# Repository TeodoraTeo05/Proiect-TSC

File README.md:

# Proiect TSC 2025 – OpenBook

## Descriere generală

OpenBook este un dispozitiv portabil de tip e-book reader bazat pe ESP32-C6. Dispozitivul conține un ecran e-paper, butoane de control, senzor de mediu, ceas de timp real și posibilitate de alimentare de la baterie Li-Po, fiind gândit ca un sistem eficient energetic și scalabil.
---

#### 1 Diagramă bloc

---
## 2 BOM (Bill of Materials)

| Part | Device | Datasheet |
|------|--------|-----------|
| CHG_LED | ADAFRUIT_LEDCHIP-LED0603 | [ADAFRUIT_LEDCHIP-LED0603](N/A) |
| SJ1 | SJ | [SJ](N/A) |
| EPD_C5 | EAGLE-LTSPICE_CC0402 | [EAGLE-LTSPICE_CC0402](N/A) |
| R3 | ESP32_WROVER_EAGLE-LTSPICE_RR0402 | [ESP32_WROVER_EAGLE-LTSPICE_RR0402](N/A) |
| R1_PWRUSB | ESP32_WROVER_EAGLE-LTSPICE_RR0402 | [ESP32_WROVER_EAGLE-LTSPICE_RR0402](N/A) |
| C4_USB | EAGLE-LTSPICE_CC0402 | [EAGLE-LTSPICE_CC0402](N/A) |
| C1, C2, C6, C8, C9, C10, C_DELAY | ESP32_WROVER_EAGLE-LTSPICE_CC0402 | [ESP32_WROVER_EAGLE-LTSPICE_CC0402](N/A) |
| C3 | RCL_CPOL-EUCT3528 | [RCL_CPOL-EUCT3528](N/A) |
| R1, R1_PINH, R1_PINH1, R2_PINH, R2_PINH1, R4, R5, R6, R7, R8, R9, R10, R_BOOT, R_CHANGE, R_CL1, R_RESET | ESP32_WROVER_EAGLE-LTSPICE_RR0402 | [ESP32_WROVER_EAGLE-LTSPICE_RR0402](N/A) |
| C7 | ESP32_WROVER_EAGLE-LTSPICE_CC0402 | [ESP32_WROVER_EAGLE-LTSPICE_CC0402](N/A) |
| J4 | 112A-TAAR-R03_ATTEND | [112A-TAAR-R03_ATTEND](N/A) |
| R_CAPACITOR | ESP32_WROVER_EAGLE-LTSPICE_RR0402 | [ESP32_WROVER_EAGLE-LTSPICE_RR0402](N/A) |
| C5 | ESP32_WROVER_EAGLE-LTSPICE_CC0402 | [ESP32_WROVER_EAGLE-LTSPICE_CC0402](N/A) |
| EPD_C6, EPD_C7, EPD_C8, EPD_C9, EPD_C10, EPD_C11, EPD_C12 | EAGLE-LTSPICE_CC0402 | [EAGLE-LTSPICE_CC0402](N/A) |
| EPD_C1, EPD_C2 | ESP32_WROVER_EAGLE-LTSPICE_CC0402 | [ESP32_WROVER_EAGLE-LTSPICE_CC0402](N/A) |
| R2 | ESP32_WROVER_EAGLE-LTSPICE_RR0402 | [ESP32_WROVER_EAGLE-LTSPICE_RR0402](N/A) |
| R1_BAT | ESP32_WROVER_EAGLE-LTSPICE_RR0402 | [ESP32_WROVER_EAGLE-LTSPICE_RR0402](N/A) |
| Q1, Q2 | ESP32_WROVER_SPARKFUN-DISCRETESEMI_MOSFET_PCH-DMG2305UX-7 | [ESP32_WROVER_SPARKFUN-DISCRETESEMI_MOSFET_PCH-DMG2305UX-7](N/A) |
| R2_BAT | ESP32_WROVER_EAGLE-LTSPICE_RR0402 | [ESP32_WROVER_EAGLE-LTSPICE_RR0402](N/A) |
| C5_USB | EAGLE-LTSPICE_CC0402 | [EAGLE-LTSPICE_CC0402](N/A) |
| C1_BAT, C1_BAT1, C1_BAT2, C2_BAT | ESP32_WROVER_EAGLE-LTSPICE_CC0402 | [ESP32_WROVER_EAGLE-LTSPICE_CC0402](N/A) |
| C4 | ESP32_WROVER_EAGLE-LTSPICE_CC0402 | [ESP32_WROVER_EAGLE-LTSPICE_CC0402](N/A) |
| R2-USB, R2-USB1 | ESP32_WROVER_EAGLE-LTSPICE_RR0402 | [ESP32_WROVER_EAGLE-LTSPICE_RR0402](N/A) |
| L1 | 744043680IND_4828-WE-TPC_WRE | [744043680IND_4828-WE-TPC_WRE](N/A) |
| IC1 | BD5229G-TR | [BD5229G-TR](N/A) |
| SENSOR2 | ESP32_WROVER_BME680_BME680 | [ESP32_WROVER_BME680_BME680](N/A) |
| U$2 | BUTTON_CUSYOMV1 | [BUTTON_CUSYOMV1](N/A) |
| U$3 | BUTTON_CUSYOMV1 | [BUTTON_CUSYOMV1](N/A) |
| C10_SUPERCAP | CPH3225A | [CPH3225A](https://www.snapeda.com/parts/CPH3225A/Seiko+Instruments/view-part/?ref=snap) |
| U3 | DS3231SN# | [DS3231SN#](https://www.snapeda.com/parts/DS3231SN%23/Analog+Devices/view-part/?ref=snap) |
| U2 | ESP32-C6-WROOM-1-N8 | [ESP32-C6-WROOM-1-N8](N/A) |
| PFMF.050.1 | ESP32C6_VARISTORCN1812 | [ESP32C6_VARISTORCN1812](N/A) |
| D2, D7 | ESP32_WROVER_AVX---SD0805S020S1R0_AVX_SD0805S020S1R0_0_0AVX_SD0805S020S1R0_0_0 | [ESP32_WROVER_AVX---SD0805S020S1R0_AVX_SD0805S020S1R0_0_0AVX_SD0805S020S1R0_0_0](N/A) |
| MCP73831 | ESP32_WROVER_SPARKFUN-IC-POWER_MCP73831 | [ESP32_WROVER_SPARKFUN-IC-POWER_MCP73831](N/A) |
| J1 | FH34SRJ-24S-0.5SH_99_ | [FH34SRJ-24S-0.5SH_99_](N/A) |
| U4 | MAX17048G+T10 | [MAX17048G+T10](https://www.snapeda.com/parts/MAX17048G+T10/Analog+Devices/view-part/?ref=snap) |
| D3, D4, D5 | MBR0530 | [MBR0530](https://www.snapeda.com/parts/MBR0530/Onsemi/view-part/?ref=snap) |
| D6, D8, D9, D10, D11, D12 | PGB1010603MR | [PGB1010603MR](https://www.snapeda.com/parts/PGB1010603MR/Littelfuse/view-part/?ref=snap) |
| J3 | QWIIC_CONNECTORJS-1MM | [QWIIC_CONNECTORJS-1MM](N/A) |
| U$1 | BUTTON_CUSYOMV1 | [BUTTON_CUSYOMV1](N/A) |
| J2 | SAMACSYS_PARTS_USB4110-GF-A | [SAMACSYS_PARTS_USB4110-GF-A](N/A) |
| Q3 | SI1308EDL-T1-GE3 | [SI1308EDL-T1-GE3](N/A) |
| TP1, TP2, TP3, TP4, TP5, TP6, TP7, TP8, TP9, TP10, TP11, TP12, TP13, TP14, TP15, TP16, TP17 | TPTP20R | [facut de mine] |
| D1 | USBLC6-2SC6Y | [USBLC6-2SC6Y](https://www.snapeda.com/parts/USBLC6-2SC6Y/STMicroelectronics/view-part/?ref=snap) |
| U1 | W25Q512JVEIQ | [W25Q512JVEIQ](https://www.snapeda.com/parts/W25Q512JVEIQ/Winbond+Electronics/view-part/?ref=snap) |
| IC4 | XC6220A331MR-G | [XC6220A331MR-G](N/A) |

## 3. Funcționalitate hardware

Proiectul OpenBook este un cititor de tip e-paper, alimentat din baterie LiPo și construit în jurul microcontrollerului ESP32-C3-WROOM. 
Dispozitivul colectează date de mediu (temperatură, umiditate, CO2, particule), le salvează pe card microSD și le poate afișa pe ecranul e-paper.

### ESP32-C3-WROOM
- Modulul principal cu conectivitate Wi-Fi/BLE, capabil să comunice prin SPI, I2C și UART.
- Tensiune de alimentare: 3.3V, furnizată de LDO.

### Sistem de alimentare
- **USB-C** este utilizat pentru încărcare și comunicare USB.
- **MCP73832** gestionează încărcarea bateriei LiPo.
- **LDO 3.3V** alimentează ESP32 și restul componentelor la 3.3V.
- **DC/DC 5V** generează 5V pentru senzorii care necesită tensiune mai mare (PM și CO2).

### Senzori
- **BME680** - senzor de temperatură, umiditate și gaze, comunică prin I2C.
- **MH-Z19B** - senzor de CO2 alimentat la 5V, comunică prin UART.
- **PMSA003** - senzor pentru particule fine (PM2.5), comunică prin UART, 5V.

### Afișaj
- Display e-paper monocrom de 1.5" cu rezoluție 200x200 px.
- Interfață SPI comună cu SD Card-ul.

### SD Card
- Modul pentru stocarea datelor colectate sau a fișierelor text.
- Interfață SPI.

### Butoane
- 3 butoane tactile conectate la GPIO pentru control interfață (ex. navigare meniu, refresh ecran).

### Calcule de consum estimativ (valori medii)

| Modul                | Tensiune | Curent (mA) | Consum estimativ |
|----------------------|----------|-------------|------------------|
| ESP32-C3             | 3.3V     | 80-150       | 0.3-0.5W         |
| E-Ink Display        | 3.3V     | 10 (refresh) | 0.03W            |
| BME680               | 3.3V     | 2-3          | 0.01W            |
| MH-Z19B              | 5V       | 40-50        | 0.25W            |
| PMSA003              | 5V       | 60-100       | 0.5W             |
| SD Card              | 3.3V     | 10           | 0.03W            |
| MCP73832 (charger)   | 5V       | 1000 (max)   | doar când încarcă |

**Modul deep sleep:** Consum sub 1 mA total. Ideal pentru dispozitiv portabil.

## 4. Pinout ESP32-C3

| Pin ESP32-C3     | Componentă                 | Motiv / Semnal                          |
|------------------|------------------------------|-----------------------------------------|
| GPIO1 (I2C SDA)  | BME680                       | Comunicație I2C                       |
| GPIO2 (I2C SCL)  | BME680                       | Comunicație I2C                       |
| GPIO3 (UART RX)  | PMSA003                      | UART RX senzor PM                       |
| GPIO4 (SPI CS SD)| SD Card                      | Chip Select SD Card                     |
| GPIO5            | E-Ink DC                     | Date/Command E-Ink                      |
| GPIO6 (SPI CLK)  | E-Ink & SD                   | Clock SPI                              |
| GPIO7 (SPI MOSI) | E-Ink & SD                   | Date SPI                               |
| GPIO8 (GPIO)     | Buton 1                      | Control meniu / page flip              |
| GPIO9 (GPIO)     | Buton 2                      | Control meniu / page flip              |
| GPIO10 (SPI CS)  | E-Ink Display                | Chip Select e-paper                    |
| GPIO11 (SPI CS)  | Flash extern (opțional)     | N/A                                    |
| GPIO12 (USB D-)  | USB                          | Comunicație USB                       |
| GPIO13 (USB D+)  | USB                          | Comunicație USB                       |
| GPIO18           | MH-Z19B (UART TX)            | UART pentru senzor CO2                 |
| GPIO19           | Buton 3                      | Navigare / confirmare                  |

## 5. Alte aspecte relevante

- Designul PCB respectă recomandările de trasee de putere (min 0.3mm), semnale (min 0.15mm).
- Antena ESP32-C3 este amplasată spre exteriorul plăcii, iar zona de sub ea este decupată.
- Condensatoarele de decuplare sunt apropiate de VCC-ul componentelor.
- Plan de masă solid pe ambele layere și via stitching activ.
- Toate componentele pasive sunt SMD 0402.
- Layout-ul este proiectat în Fusion360, aliniat cu dimensiunile carcasei fizice.
- Imaginile randate ale dispozitivului și carcasei se găsesc în folderul `Images/` din acest repository.

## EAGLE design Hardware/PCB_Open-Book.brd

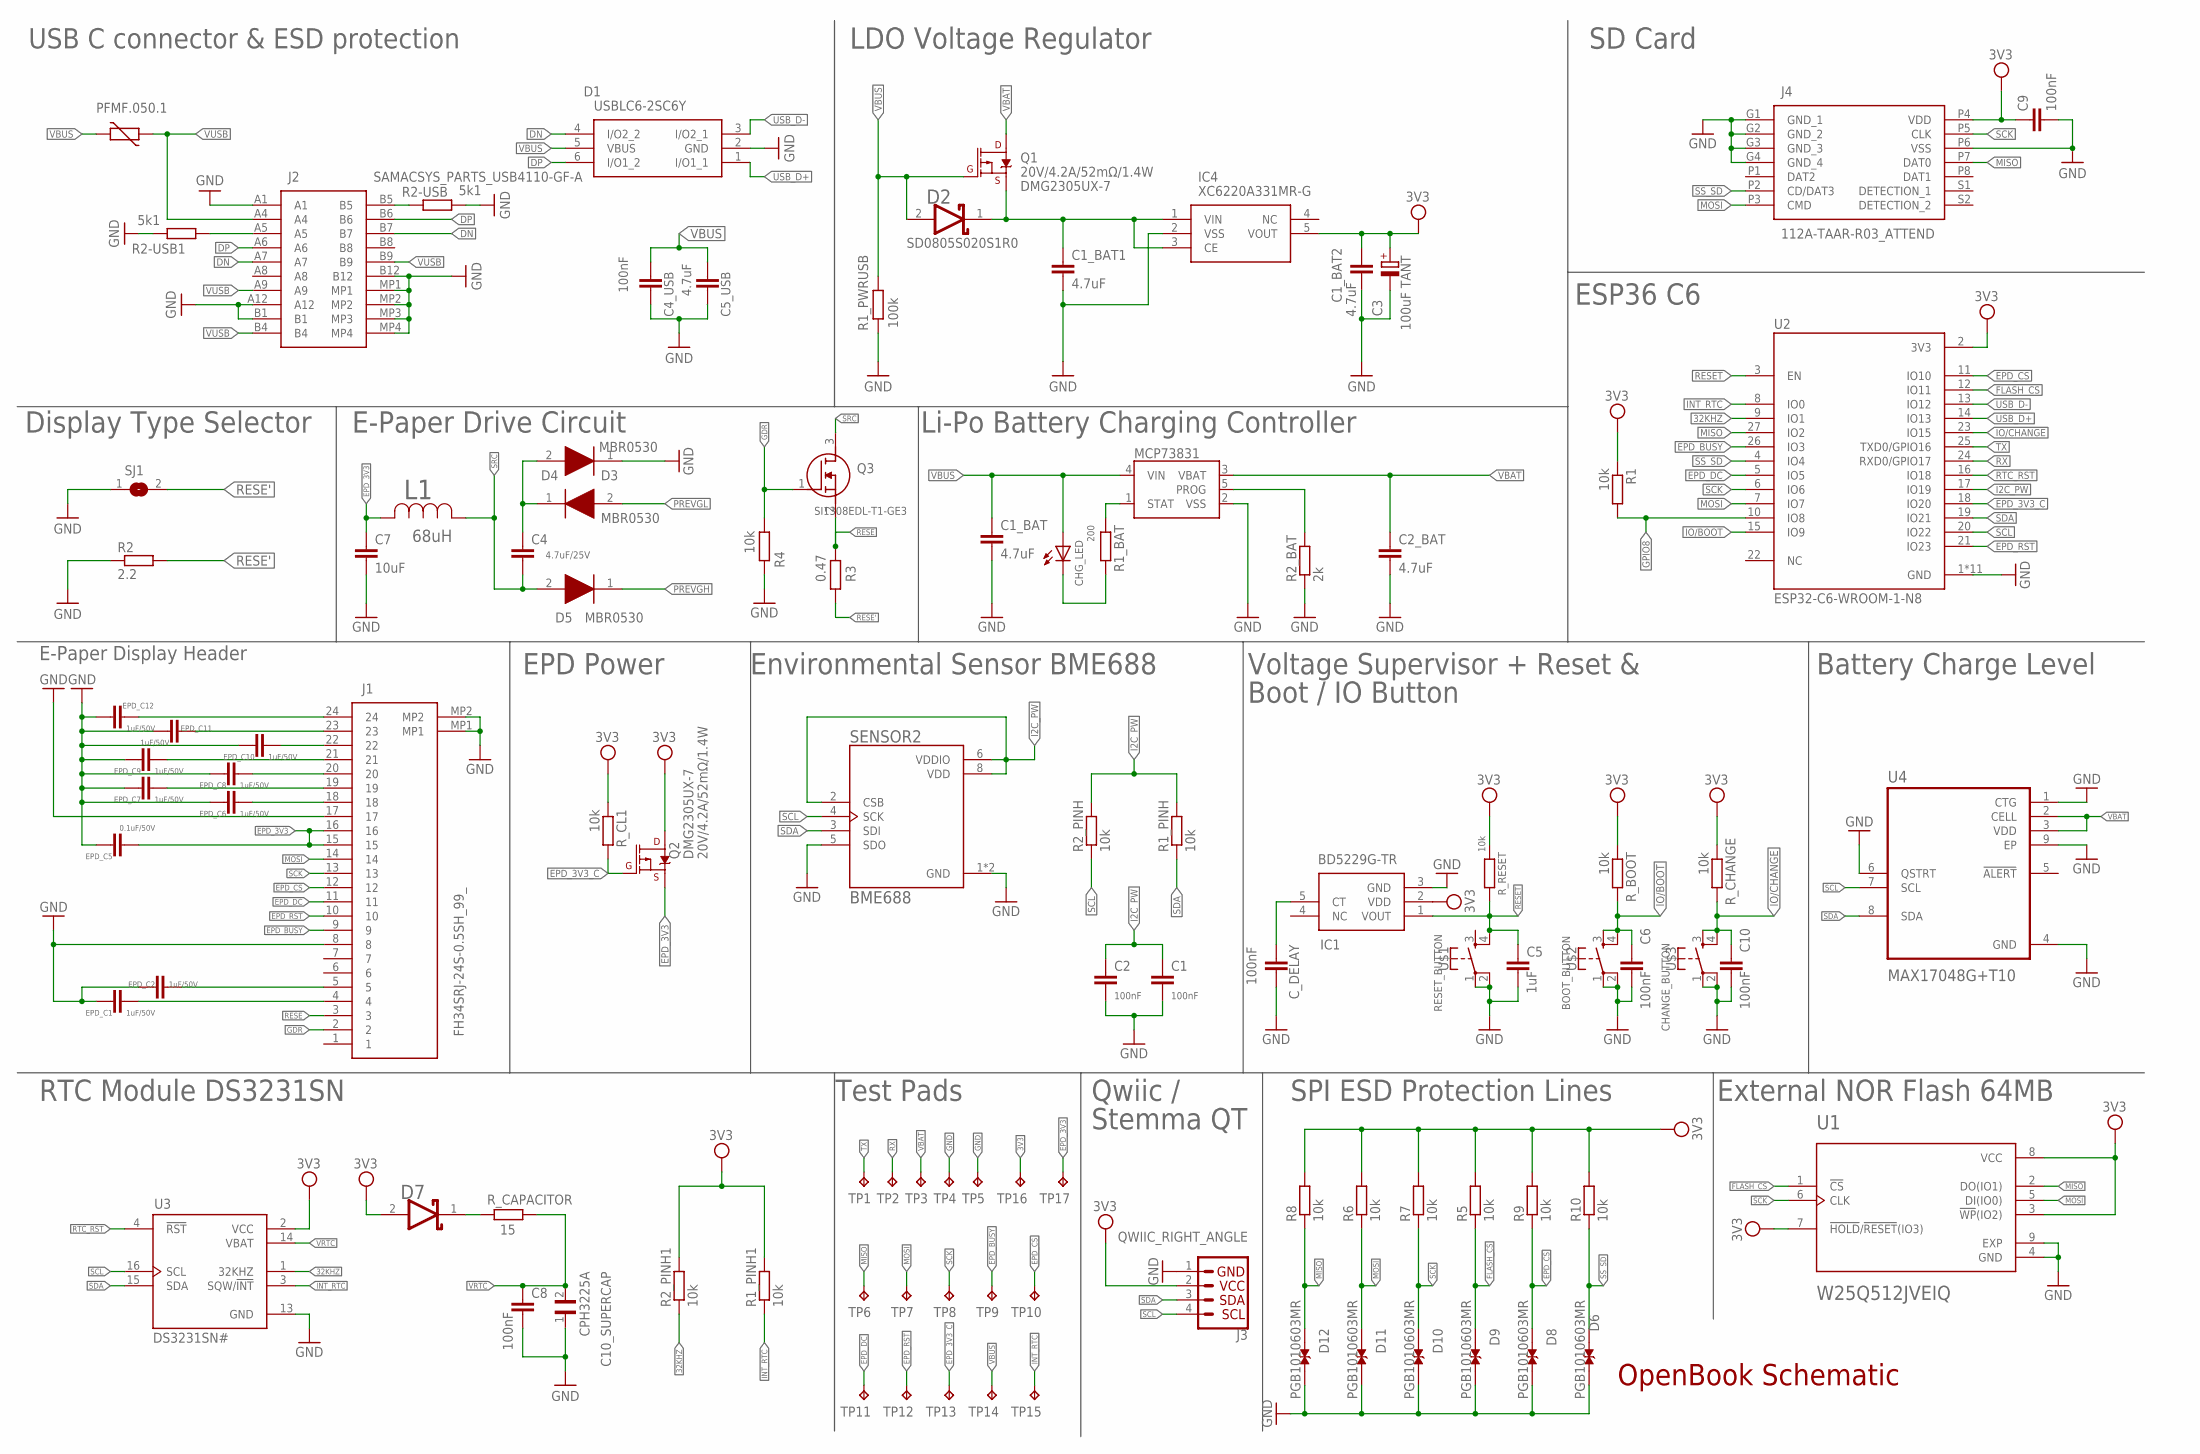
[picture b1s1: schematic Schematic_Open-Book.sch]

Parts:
C1, C2, C6, C8, C9, C10: 100nF; ESP32_WROVER_EAGLE-LTSPICE_C0402
C1_BAT, C1_BAT1, C1_BAT2, C2_BAT: 4.7uF; ESP32_WROVER_EAGLE-LTSPICE_C0402
C3: 100uF TANT; RCL_CT3528
C4: 4.7uF/25V; ESP32_WROVER_EAGLE-LTSPICE_C0402
C4_USB: 100nF; EAGLE-LTSPICE_C0402
C5: 1uF; ESP32_WROVER_EAGLE-LTSPICE_C0402
C5_USB: 4.7uF; EAGLE-LTSPICE_C0402
C7: 10uF; ESP32_WROVER_EAGLE-LTSPICE_C0402
C10_SUPERCAP: CPH3225A; CAPCP3225X100N
CHG_LED: ADAFRUIT_LEDCHIP-LED0603; ADAFRUIT_CHIP-LED0603
C_DELAY: 100nF; ESP32_WROVER_EAGLE-LTSPICE_C0402
D1: USBLC6-2SC6Y; SOT95P280X145-6N
D2, D7: ESP32_WROVER_AVX---SD0805S020S1R0_AVX_SD0805S020S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; ESP32_WROVER_AVX---SD0805S020S1R0_AVX_SD0805S020S1R0_0
D3, D4, D5: MBR0530; SOD3716X135N
D6, D8, D9, D10, D11, D12: PGB1010603MR; DIOC1608X36N
EPD_C1, EPD_C2: 1uF/50V; ESP32_WROVER_EAGLE-LTSPICE_C0402
EPD_C5: 0.1uF/50V; EAGLE-LTSPICE_C0402
EPD_C6, EPD_C7, EPD_C8, EPD_C9, EPD_C10, EPD_C11, EPD_C12: 1uF/50V; EAGLE-LTSPICE_C0402
IC1: BD5229G-TR; SOT95P280X125-5N
IC4: XC6220A331MR-G; SOT95P280X120-5N
J1: FH34SRJ-24S-0.5SH_99_; FH34SRJ24S05SH99
J2: SAMACSYS_PARTS_USB4110-GF-A; SAMACSYS_PARTS_USB4110GFA
J3: QWIIC_RIGHT_ANGLE; JST04_1MM_RA
J4: 112A-TAAR-R03_ATTEND; 112ATAARR03ATTEND
L1: 68uH; IND_4828-WE-TPC_WRE
MCP73831: ESP32_WROVER_SPARKFUN-IC-POWER_MCP73831; ESP32_WROVER_SPARKFUN-IC-POWER_SOT23-5
PFMF.050.1: ESP32C6_VARISTORCN1812; ESP32C6_VARISTOR_CT/CN1812
Q1, Q2: 20V/4.2A/52mΩ/1.4W; ESP32_WROVER_SPARKFUN-DISCRETESEMI_SOT23-3
Q3: SI1308EDL-T1-GE3; SOT65P210X110-3N
R1, R1_PINH, R1_PINH1, R2_PINH, R2_PINH1, R4, R5, R6, R7, R8, R9, R10: 10k; ESP32_WROVER_EAGLE-LTSPICE_R0402
R1_BAT: 200; ESP32_WROVER_EAGLE-LTSPICE_R0402
R1_PWRUSB: 100k; ESP32_WROVER_EAGLE-LTSPICE_R0402
R2: 2.2; ESP32_WROVER_EAGLE-LTSPICE_R0402
R2-USB, R2-USB1: 5k1; ESP32_WROVER_EAGLE-LTSPICE_R0402
R2_BAT: 2k; ESP32_WROVER_EAGLE-LTSPICE_R0402
R3: 0.47; ESP32_WROVER_EAGLE-LTSPICE_R0402
R_BOOT: 10k; ESP32_WROVER_EAGLE-LTSPICE_R0402
R_CAPACITOR: 15; ESP32_WROVER_EAGLE-LTSPICE_R0402
R_CHANGE: 10k; ESP32_WROVER_EAGLE-LTSPICE_R0402
R_CL1: 10k; ESP32_WROVER_EAGLE-LTSPICE_R0402
R_RESET: 10k; ESP32_WROVER_EAGLE-LTSPICE_R0402
SENSOR2: BME688; ESP32_WROVER_BME680_PSON80P300X300X100-8N
SJ1: SJ
TP1, TP2, TP3, TP4, TP5, TP6, TP7, TP8, TP9, TP10, TP11, TP12, TP13, TP14, TP15, TP16, TP17: TPTP20R; TP20R
U1: W25Q512JVEIQ; SON127P600X800X80-9N
U2: ESP32-C6-WROOM-1-N8; XCVR_ESP32-C6-WROOM-1-N8
U3: DS3231SN#; SOIC127P1032X265-16N
U4: MAX17048G+T10; SON50P200X200X80-9N
U$1: RESET_BUTTON; MYBUTTON
U$2: BOOT_BUTTON; MYBUTTON
U$3: CHANGE_BUTTON; MYBUTTON

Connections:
3V3: C1_BAT2.1, C3.+, C9.1, D7.2 (ANODE), IC1.2 (VDD), IC4.5 (VOUT), J3.2, J4.P4 (VDD), Q2.3 (D), R1.1, R1_PINH1.2, R2_PINH1.2, R5.2, R6.2, R7.2, R8.2, R9.2, R10.2, R_BOOT.1, R_CHANGE.1, R_CL1.1, R_RESET.1, TP16.TP, U1.3 (!WP!(IO2)), U1.7 (!HOLD!/!RESET!(IO3)), U1.8 (VCC), U2.2 (3V3), U3.2 (VCC)
32KHZ: R2_PINH1.1, U2.9 (IO1), U3.1 (32KHZ)
DN: D1.4 (I/O2_2), J2.A7, J2.B7
DP: D1.6 (I/O1_2), J2.A6, J2.B6
EPD_3V3: C7.1, EPD_C5.1, J1.15, J1.16, L1.2, Q2.2 (S), TP17.TP
EPD_3V3_C: Q2.1 (G), R_CL1.2, TP13.TP, U2.18 (IO20)
EPD_BUSY: J1.9, TP9.TP, U2.26 (IO3)
EPD_CS: D8.1, J1.12, R9.1, TP10.TP, U2.11 (IO10)
EPD_DC: J1.11, TP11.TP, U2.5 (IO5)
EPD_RST: J1.10, TP12.TP, U2.21 (IO23)
FLASH_CS: D9.1, R5.1, U1.1 (!CS), U2.12 (IO11)
GDR: J1.2, Q3.1 (G), R4.2
GND: C1.2, C1_BAT.2, C1_BAT1.2, C1_BAT2.2, C2.2, C2_BAT.2, C3.-, C4_USB.2, C5.2, C5_USB.2, C6.2, C7.2, C8.2, C9.2, C10.2, C10_SUPERCAP.1, C_DELAY.2, D1.2 (GND), D4.1 (K), D6.2, D8.2, D9.2, D10.2, D11.2, D12.2, EPD_C1.2, EPD_C2.2, EPD_C5.2, EPD_C6.2, EPD_C7.2, EPD_C8.2, EPD_C9.2, EPD_C10.2, EPD_C11.2, EPD_C12.2, IC1.3 (GND), IC4.2 (VSS), J1.8, J1.17, J1.MP1, J1.MP2, J2.A1, J2.A12, J2.B1, J2.B12, J2.MP1, J2.MP2, J2.MP3, J2.MP4, J3.1, J4.G1 (GND_1), J4.G2 (GND_2), J4.G3 (GND_3), J4.G4 (GND_4), J4.P6 (VSS), MCP73831.2 (VSS), R1_PWRUSB.2, R2.1, R2-USB.2, R2-USB1.1, R2_BAT.1, R4.1, SENSOR2.1 (GND), SENSOR2.5 (SDO), SENSOR2.7 (GND), SJ1.1, TP4.TP, TP5.TP, U1.4 (GND), U1.9 (EXP), U2.1 (GND), U2.28 (GND), U2.29_1 (GND), U2.29_2 (GND), U2.29_3 (GND), U2.29_4 (GND), U2.29_5 (GND), U2.29_6 (GND), U2.29_7 (GND), U2.29_8 (GND), U2.29_9 (GND), U3.13 (GND), U4.1 (CTG), U4.4 (GND), U4.6 (QSTRT), U4.9 (EP), U$1.1, U$1.2, U$2.1, U$2.2, U$3.1, U$3.2
GPIO8: R1.2, U2.10 (IO8)
I2C_PW: C1.1, C2.1, R1_PINH.2, R2_PINH.2, SENSOR2.2 (CSB), SENSOR2.6 (VDDIO), SENSOR2.8 (VDD), U2.17 (IO19)
INT_RTC: R1_PINH1.1, TP15.TP, U2.8 (IO0), U3.3 (SQW/!INT)
IO/BOOT: C6.1, R_BOOT.2, U2.15 (IO9), U$2.3, U$2.4
IO/CHANGE: C10.1, R_CHANGE.2, U2.23 (IO15), U$3.3, U$3.4
MISO: D12.1, J4.P7 (DAT0), R8.1, TP6.TP, U1.2 (DO(IO1)), U2.27 (IO2)
MOSI: D11.1, J1.14, J4.P3 (CMD), R6.1, TP7.TP, U1.5 (DI(IO0)), U2.7 (IO7)
unnamed: J2.B5, R2-USB.1
unnamed: J2.A5, R2-USB1.2
unnamed: C4.1, D3.1 (K), D4.2 (A)
unnamed: C1_BAT1.1, D2.1 (CATHODE), IC4.1 (VIN), IC4.3 (CE), Q1.2 (S)
unnamed: MCP73831.5 (PROG), R2_BAT.2
unnamed: CHG_LED.C, R1_BAT.2
unnamed: MCP73831.1 (STAT), R1_BAT.1
unnamed: C_DELAY.1, IC1.5 (CT)
unnamed: EPD_C2.1, J1.5
unnamed: EPD_C1.1, J1.4
unnamed: D7.1 (CATHODE), R_CAPACITOR.2
unnamed: EPD_C12.1, J1.24
unnamed: EPD_C11.1, J1.23
unnamed: EPD_C10.1, J1.22
unnamed: EPD_C8.1, J1.20
unnamed: EPD_C7.1, J1.19
unnamed: EPD_C9.1, J1.21
unnamed: EPD_C6.1, J1.18
PREVGH: D5.1 (K)
PREVGL: D3.2 (A)
RESE: J1.3, Q3.2 (S), R3.2
RESE': R2.2, R3.1, SJ1.2
RESET: C5.1, IC1.1 (VOUT), R_RESET.2, U2.3 (EN), U$1.4
RTC_RST: U2.16 (IO18), U3.4 (!RST)
RX: TP2.TP, U2.24 (RXD0/GPIO17)
SCK: D10.1, J1.13, J4.P5 (CLK), R7.1, TP8.TP, U1.6 (CLK), U2.6 (IO6)
SCL: J3.4, R2_PINH.1, SENSOR2.4 (SCK), U2.20 (IO22), U3.16 (SCL), U4.7 (SCL)
SDA: J3.3, R1_PINH.1, SENSOR2.3 (SDI), U2.19 (IO21), U3.15 (SDA), U4.8 (SDA)
SRC: C4.2, D5.2 (A), L1.1, Q3.3 (D)
SS_SD: D6.1, J4.P2 (CD/DAT3), R10.1, U2.4 (IO4)
TX: TP1.TP, U2.25 (TXD0/GPIO16)
USB_D+: D1.1 (I/O1_1), U2.14 (IO13)
USB_D-: D1.3 (I/O2_1), U2.13 (IO12)
VBAT: C2_BAT.1, MCP73831.3 (VBAT), Q1.3 (D), TP3.TP, U4.2 (CELL), U4.3 (VDD)
VBUS: C1_BAT.1, C4_USB.1, C5_USB.1, CHG_LED.A, D1.5 (VBUS), D2.2 (ANODE), MCP73831.4 (VIN), PFMF.050.1.2, Q1.1 (G), R1_PWRUSB.1, TP14.TP
VRTC: C8.1, C10_SUPERCAP.2, R_CAPACITOR.1, U3.14 (VBAT)
VUSB: J2.A4, J2.A9, J2.B4, J2.B9, PFMF.050.1.1

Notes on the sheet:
USB C connector & ESD protection
LDO Voltage Regulator
SD0805S020S1R0
DMG2305UX-7
SD Card
Display Type Selector
E-Paper Drive Circuit
Li-Po Battery Charging Controller
ESP36 C6
E-Paper Display Header
EPD Power
Environmental Sensor BME688
Voltage Supervisor + Reset &
Boot / IO Button
Battery Charge Level
RTC Module DS3231SN
Test Pads
Qwiic /
Stemma QT
SPI ESD Protection Lines
External NOR Flash 64MB
OpenBook Schematic

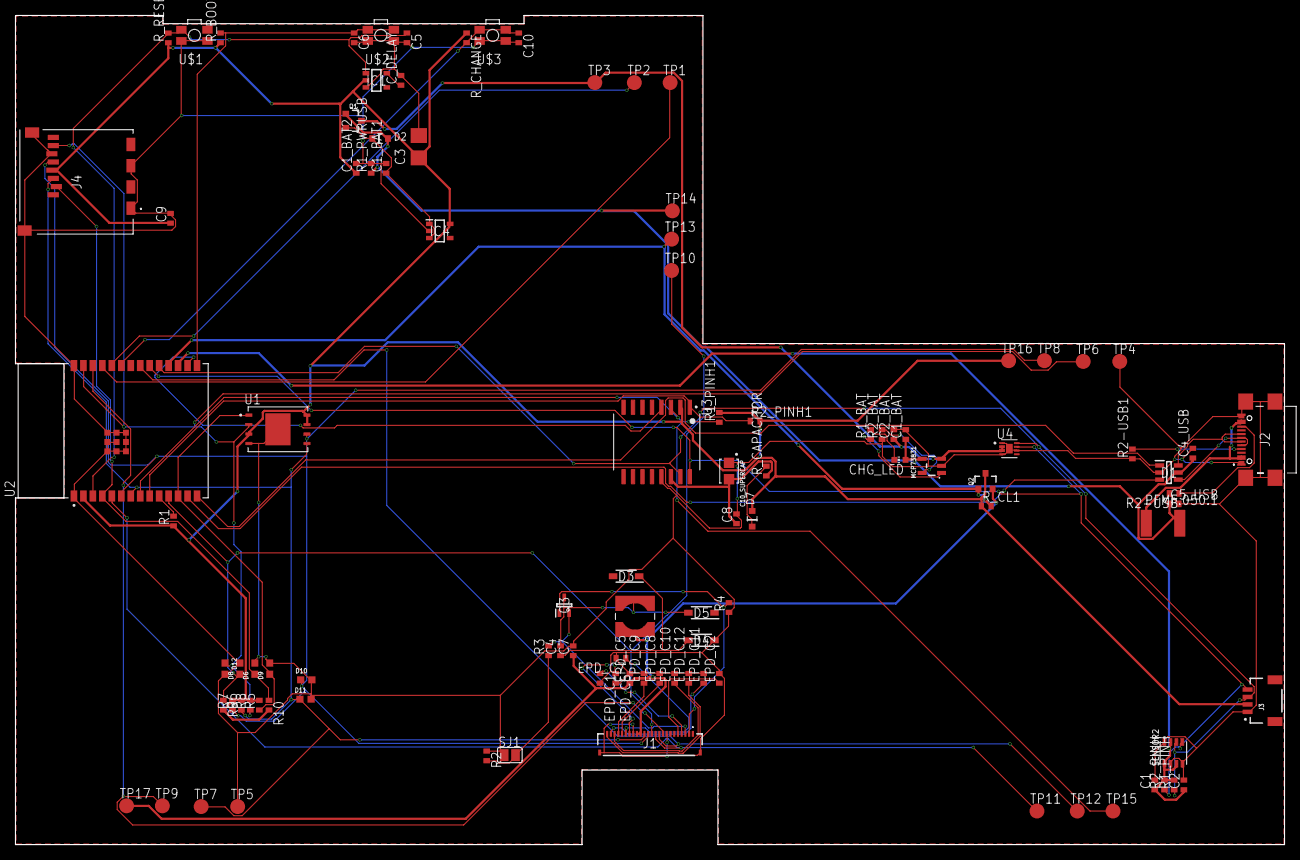
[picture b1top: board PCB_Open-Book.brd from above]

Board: 2 copper layers, 170.2 x 111.2 mm, 103 parts (0 on the bottom side), 55 nets.

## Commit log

2025-04-06 First upload
2025-04-06 Create LICENSE
2025-04-06 diagrama bloc

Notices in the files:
parts and their libraries:
COPYRIGHT: Copyright (C) 2024 Ultra Librarian. All rights reserved.
